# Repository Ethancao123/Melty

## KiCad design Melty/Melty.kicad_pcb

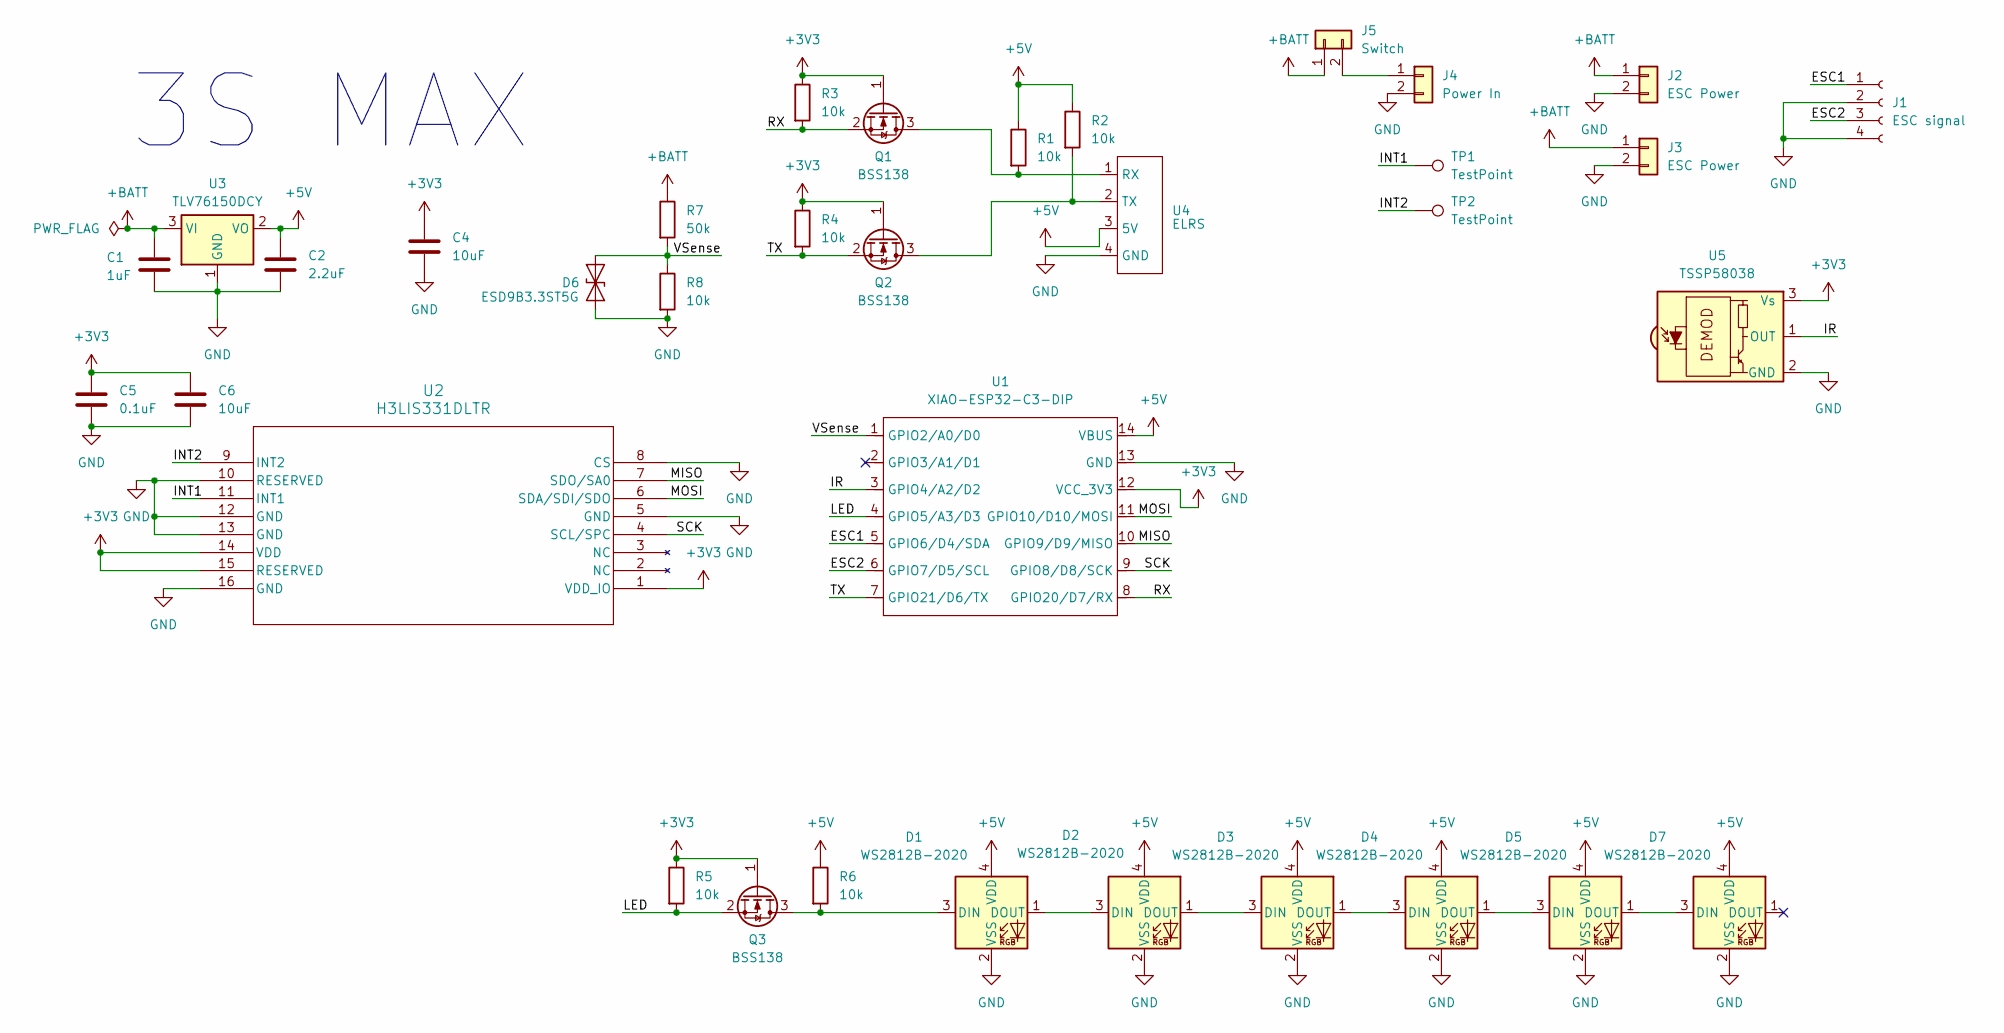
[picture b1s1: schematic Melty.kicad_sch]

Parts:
C1: 1uF; C_0603_1608Metric_Pad1.08x0.95mm_HandSolder
C2: 2.2uF; C_0603_1608Metric_Pad1.08x0.95mm_HandSolder
C4, C6: 10uF; C_0603_1608Metric_Pad1.08x0.95mm_HandSolder
C5: 0.1uF; C_0603_1608Metric_Pad1.08x0.95mm_HandSolder
D1, D2, D3, D4, D5, D7: WS2812B-2020; LED_WS2812B-2020_PLCC4_2.0x2.0mm
D6: ESD9B3.3ST5G; D_SOD-923
J1: ESC signal; JST_GH_SM04B-GHS-TB_1x04-1MP_P1.25mm_Horizontal
J2, J3: ESC Power; PowerPADS
J4: Power In; AMASS_XT30UPB-M_1x02_P5.0mm_Vertical
J5: Switch; SwitchPads
Q1, Q2, Q3: BSS138; SOT-23
R1, R2, R3, R4, R5, R6, R8: 10k; C_0603_1608Metric_Pad1.08x0.95mm_HandSolder
R7: 50k; C_0603_1608Metric_Pad1.08x0.95mm_HandSolder
TP1, TP2: TestPoint; TestPoint_Pad_D1.0mm
U1: XIAO-ESP32-C3-DIP; XIAO-ESP32S3-SMD
U2: H3LIS331DLTR; QFN_31DLTR_STM
U3: TLV76150DCY; SOT-223-3_TabPin2
U4: ELRS; BetaFPV ELRS Lite
U5: TSSP58038; Vishay_MINICAST-3Pin

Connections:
+3V3: C4.1, C5.1, C6.1, Q1.1 (G), Q2.1 (G), Q3.1 (G), R3.1, R4.1, R5.1, U1.12 (VCC_3V3), U2.1 (VDD_IO), U2.14 (VDD), U2.15 (RESERVED), U5.3 (Vs)
+5V: C2.1, D1.4 (VDD), D2.4 (VDD), D3.4 (VDD), D4.4 (VDD), D5.4 (VDD), D7.4 (VDD), R1.1, R2.1, R6.1, U1.14 (VBUS), U3.2 (VO), U4.3 (5V)
+BATT: C1.1, J2.1, J3.1, J5.1, R7.1, U3.3 (VI)
/ESC1: J1.1, U1.5 (GPIO6/D4/SDA)
/ESC2: J1.3, U1.6 (GPIO7/D5/SCL)
/INT1: TP1.1, U2.11 (INT1)
/INT2: TP2.1, U2.9 (INT2)
/IR: U1.3 (GPIO4/A2/D2), U5.1 (OUT)
/LED: Q3.2 (S), R5.2, U1.4 (GPIO5/A3/D3)
/MISO: U1.10 (GPIO9/D9/MISO), U2.7 (SDO/SA0)
/MOSI: U1.11 (GPIO10/D10/MOSI), U2.6 (SDA/SDI/SDO)
/RX: Q1.2 (S), R3.2, U1.8 (GPIO20/D7/RX)
/SCK: U1.9 (GPIO8/D8/SCK), U2.4 (SCL/SPC)
/TX: Q2.2 (S), R4.2, U1.7 (GPIO21/D6/TX)
/VSense: D6.1 (A1), R7.2, R8.1, U1.1 (GPIO2/A0/D0)
GND: C1.2, C2.2, C4.2, C5.2, C6.2, D1.2 (VSS), D2.2 (VSS), D3.2 (VSS), D4.2 (VSS), D5.2 (VSS), D6.2 (A2), D7.2 (VSS), J1.2, J1.4, J2.2, J3.2, J4.2, R8.2, U1.13 (GND), U2.5 (GND), U2.8 (CS), U2.10 (RESERVED), U2.12 (GND), U2.13 (GND), U2.16 (GND), U3.1 (GND), U4.4 (GND), U5.2 (GND)
unnamed: D1.3 (DIN), Q3.3 (D), R6.2
unnamed: D1.1 (DOUT), D2.3 (DIN)
unnamed: D2.1 (DOUT), D3.3 (DIN)
unnamed: D3.1 (DOUT), D4.3 (DIN)
unnamed: D4.1 (DOUT), D5.3 (DIN)
unnamed: D5.1 (DOUT), D7.3 (DIN)
unnamed: J4.1, J5.2
unnamed: Q1.3 (D), R1.2, U4.1 (RX)
unnamed: Q2.3 (D), R2.2, U4.2 (TX)

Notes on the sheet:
3S MAX

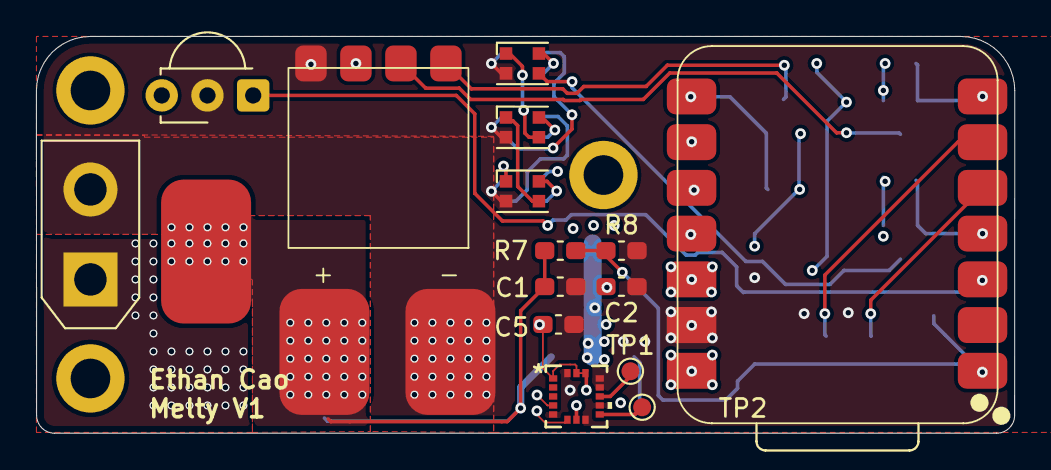
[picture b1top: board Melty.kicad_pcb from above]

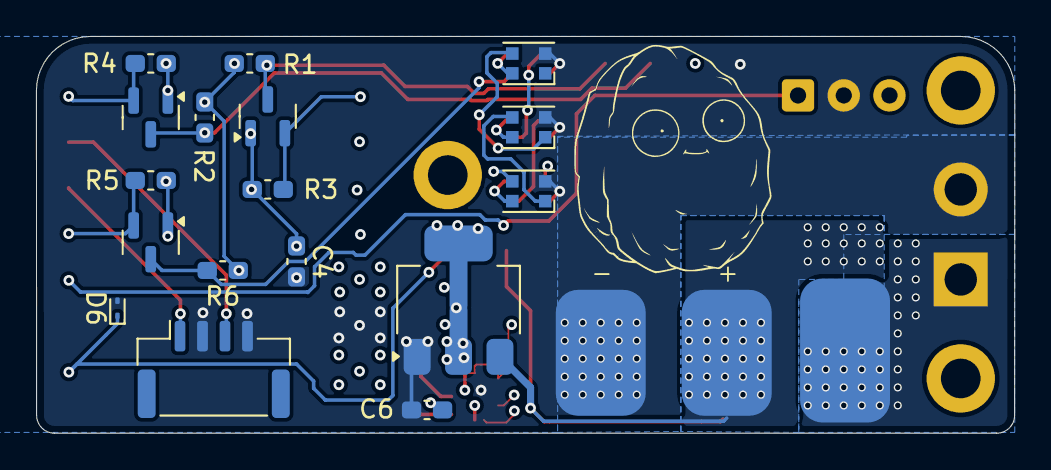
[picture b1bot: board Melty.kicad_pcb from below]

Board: 6 copper layers, 54.3 x 22.0 mm, 35 parts (18 on the bottom side), 25 nets.

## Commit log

2025-03-19 PCB V1
2025-03-19 PCB Ordered
2025-03-28 crsf reading
2025-03-29 ESC outline
2025-03-30 SPI Accel Checkpoint
2025-04-02 FASTLED BADDDD
2025-04-03 Dshot badddd
2025-06-08 DPD Robobrawl
2026-03-10 Test Stand code
